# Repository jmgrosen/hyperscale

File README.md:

# Hyperscale

A kitchen scale that helps you follow a recipe.

## Building

Export Gerbers from KiCAD for the PCB. Build STLs from OpenSCAD for the case.

An actual assembly guide is TODO!

For the firmware, install [the Xtensa rustc target](https://docs.esp-rs.org/book/installation/riscv-and-xtensa.html) and [espflash](https://docs.esp-rs.org/book/tooling/espflash.html) as described in the Rust on ESP Book. Then `cargo espflash flash`.

## Licensing

The physical design files are licensed under the CERN Open Hardware Licence Version 2 - Permissive.

The firmware code is licensed under MIT. However, due to its use of Slint, the resulting firmware as a whole is licensed under GPLv3.

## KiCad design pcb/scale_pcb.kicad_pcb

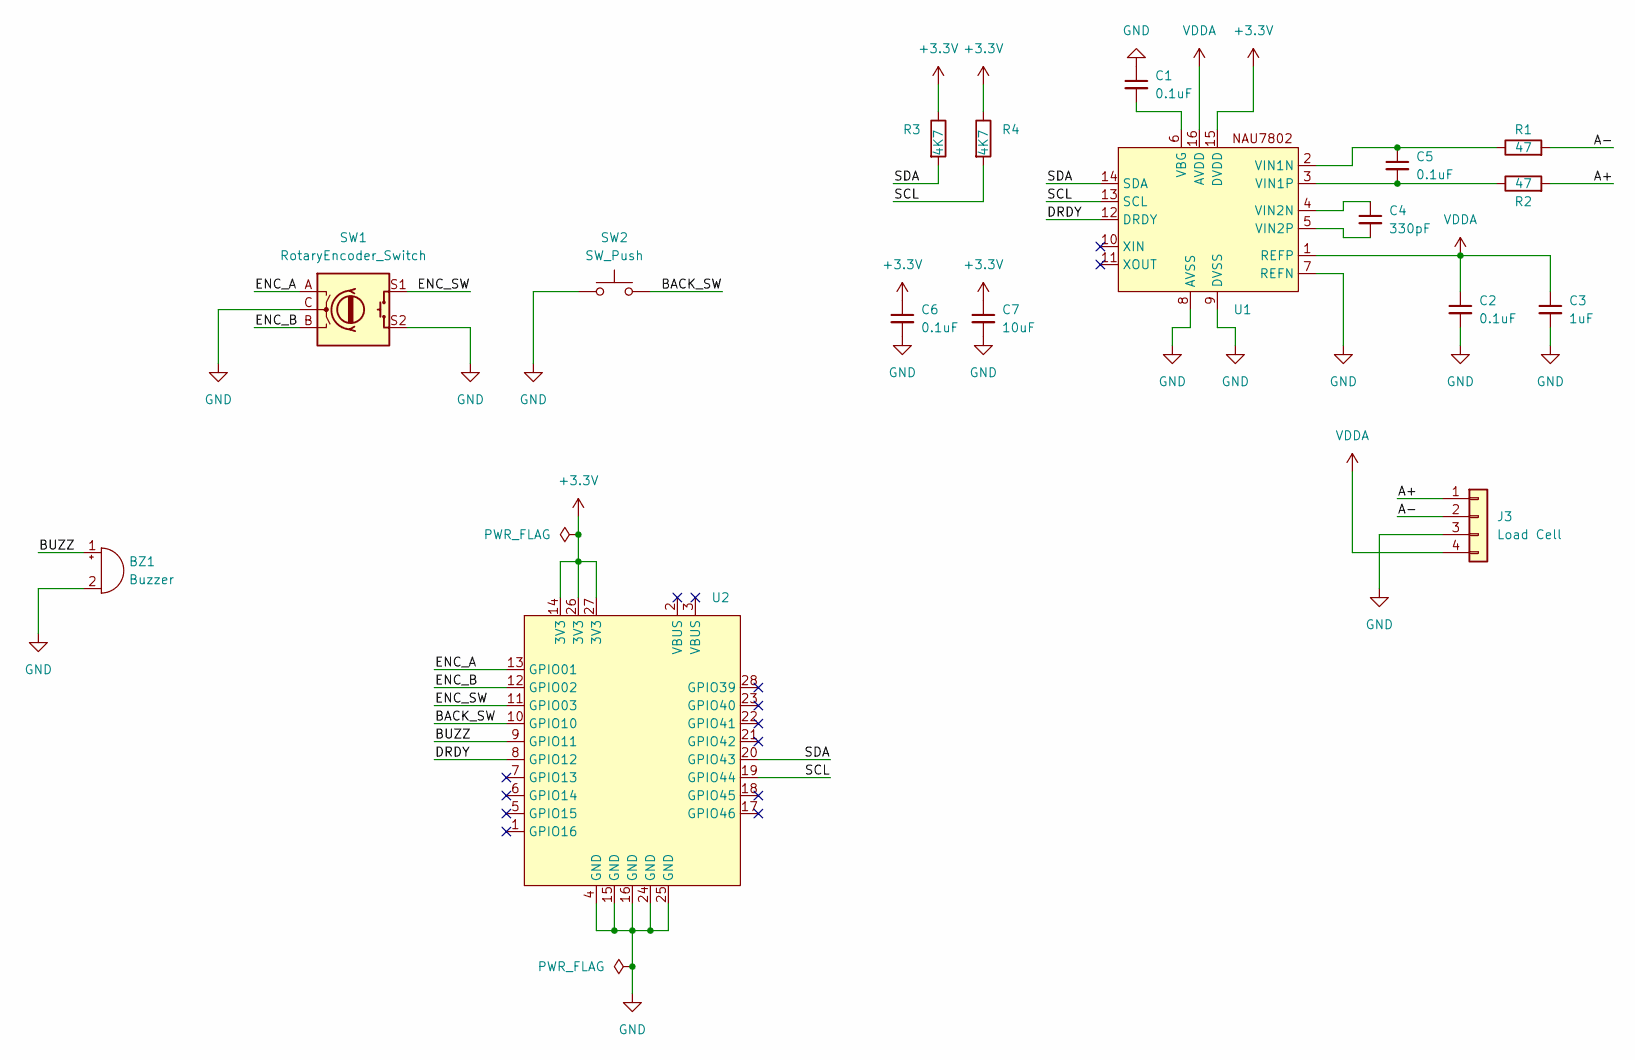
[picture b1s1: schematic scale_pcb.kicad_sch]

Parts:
BZ1: Buzzer; Buzzer_TDK_PS1240P02BT_D12.2mm_H6.5mm
C1, C2, C5, C6: 0.1uF; C_0805_2012Metric
C3: 1uF; C_0805_2012Metric
C4: 330pF; C_0805_2012Metric
C7: 10uF; C_1206_3216Metric
J3: Load Cell; PinHeader_1x04_P2.54mm_Vertical
R1, R2: 47; R_0805_2012Metric
R3, R4: 4K7; R_0805_2012Metric
SW1: RotaryEncoder_Switch; RotaryEncoder_Bourns_Vertical_PEC12R-3xxxF-Sxxxx
SW2: SW_Push; SW_PUSH-12mm
U1: SOP-16_3.9x9.9mm_P1.27mm
U2: LilyGo_T-Display-S3-AMOLED

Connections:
+3.3V: C6.1, C7.1, R3.1, R4.1, U1.15 (DVDD), U2.14 (3V3), U2.26 (3V3), U2.27 (3V3)
/A+: J3.1, R2.2
/A-: J3.2, R1.2
/BACK_SW: SW2.2, U2.10 (GPIO10)
/BUZZ: BZ1.1 (-), U2.9 (GPIO11)
/DRDY: U1.12 (DRDY), U2.8 (GPIO12)
/ENC_A: SW1.A, U2.13 (GPIO01)
/ENC_B: SW1.B, U2.12 (GPIO02)
/ENC_SW: SW1.S1, U2.11 (GPIO03)
/SCL: R4.2, U1.13 (SCL), U2.19 (GPIO44)
/SDA: R3.2, U1.14 (SDA), U2.20 (GPIO43)
GND: BZ1.2 (+), C1.1, C2.2, C3.2, C6.2, C7.2, J3.3, SW1.C, SW1.S2, SW2.1, U1.7 (REFN), U1.8 (AVSS), U1.9 (DVSS), U2.4 (GND), U2.15 (GND), U2.16 (GND), U2.24 (GND), U2.25 (GND)
unnamed: C1.2, U1.6 (VBG)
unnamed: C5.1, R1.1, U1.2 (VIN1N)
unnamed: C5.2, R2.1, U1.3 (VIN1P)
unnamed: C4.1, U1.4 (VIN2N)
unnamed: C4.2, U1.5 (VIN2P)
VDDA: C2.1, C3.1, J3.4, U1.1 (REFP), U1.16 (AVDD)

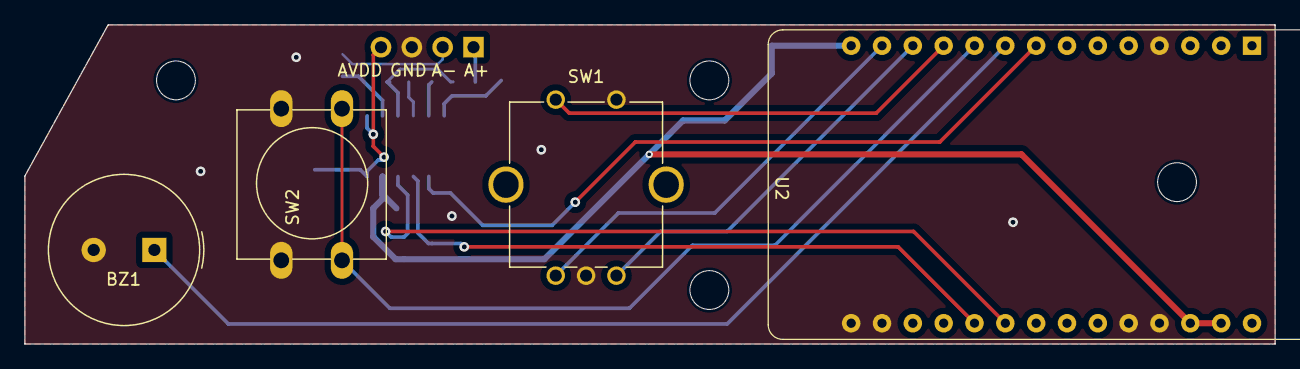
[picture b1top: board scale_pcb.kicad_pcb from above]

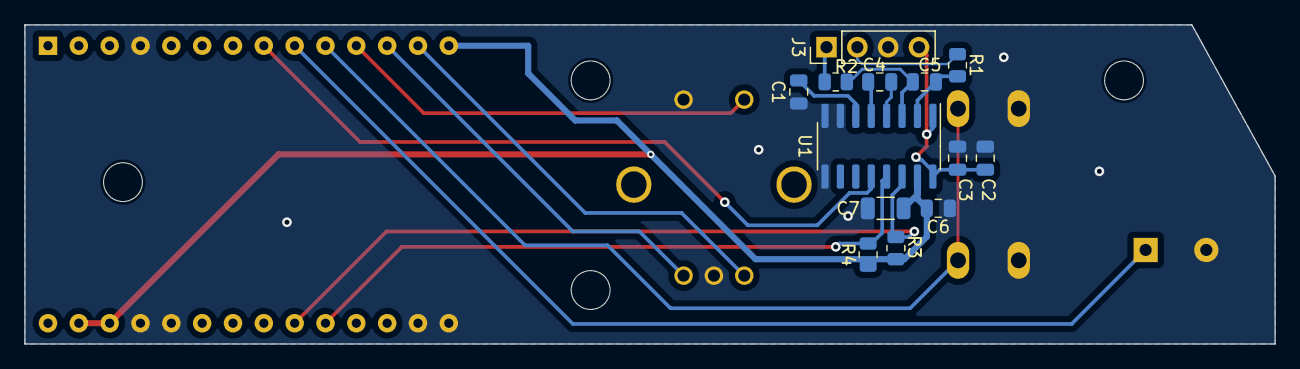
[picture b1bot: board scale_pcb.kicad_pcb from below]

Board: 2 copper layers, 103.0 x 26.3 mm, 17 parts (13 on the bottom side), 18 nets.

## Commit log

2023-12-11 initial python firmware
2023-12-25 lvgl!
2023-12-25 -> fw/
2023-12-25 add pcb
2024-01-06 case is looking good B-)
2024-01-25 did a BUNCH of stuff
2024-02-06 last python version
2024-02-09 new firmware working pretty well
2024-02-09 remove local dep
2024-08-14 clean up new-fw just a tiny bit
2024-08-18 update firmware for latest esp-hal and slint
2024-08-23 no more tearing!!
2024-10-09 fix sticky recipe progress bug
2024-10-09 increase progress bar contrast a bit
2024-10-09 add a few recipes
2024-10-17 add licenses and a minimal readme
2024-12-26 show weight at top level
2024-12-27 calibrate weight sensor in background after starting UI
2024-12-27 make invalid scale state a bit more visible
2025-06-08 add missing ingredients to creme pat recipe
2025-12-08 include cargo config file
2025-12-26 fix scrolling issues
2026-01-11 tiny reformatting in case scad
2026-01-11 add esp bootloader app desc
2026-01-11 remove extraneous scroll bars
2026-01-11 fix weight text centering on home
2026-01-25 start to get filesystem working
2026-01-25 put ui components in their own module
2026-01-25 fix warnings
2026-01-25 prep for files
2026-01-25 update edition to 2024
2026-01-25 add version file check
2026-01-25 move storage module into its own file
2026-01-25 refactor built-in recipes to prep for storage
2026-01-26 writing recipes to fs seemingly working
2026-01-26 write ordering of recipes to fs
2026-01-26 reading recipes back from fs working!
